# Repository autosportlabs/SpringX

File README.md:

SpringX
======

Strain gauge amplifier for coil spring strain gauges. Spring strain is related to force and compression, and can be used to dynamically determine suspension position.

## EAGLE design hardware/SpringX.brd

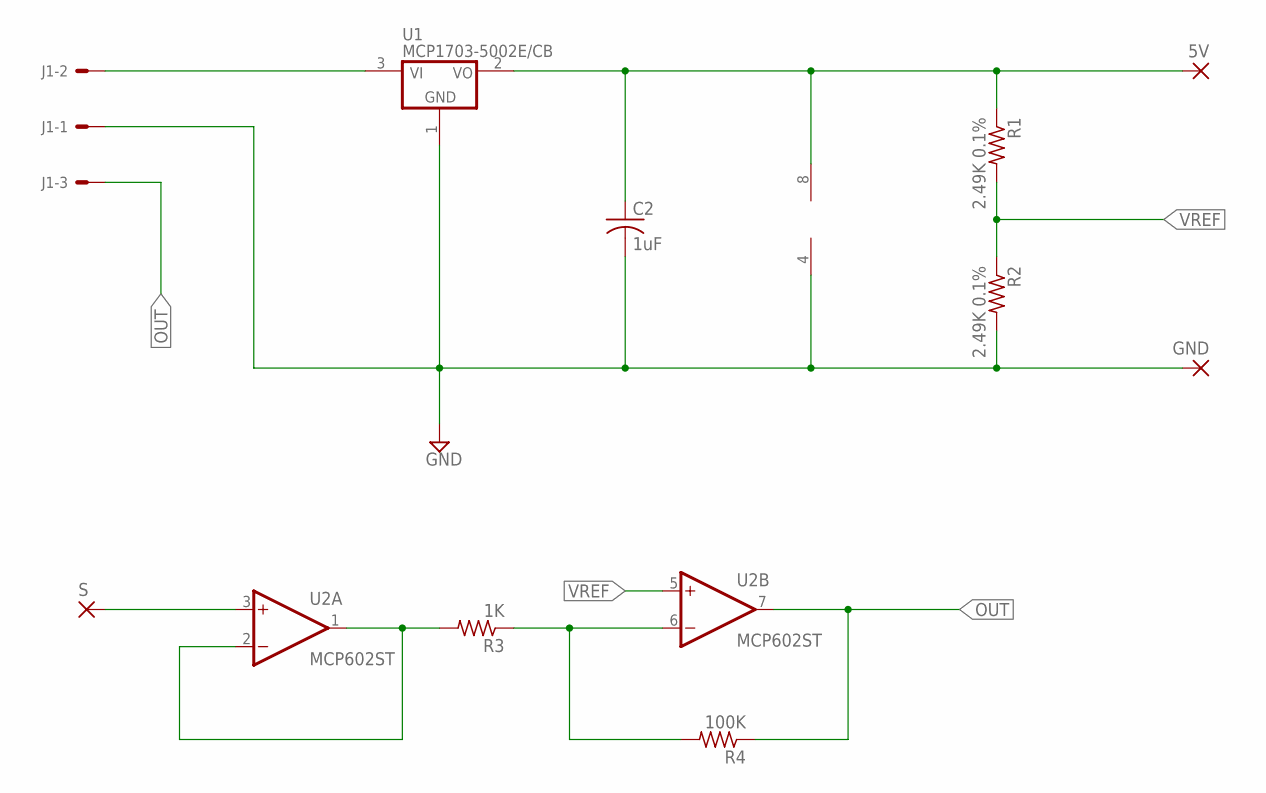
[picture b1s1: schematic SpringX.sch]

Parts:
5V: 2,15/1,0
C2: 1uF; C0603
GND: 2,15/1,0
J1: 22-05-7038-03; 7395-03
R1, R2: 2.49K 0.1%; R0603
R3: 1K; R0603
R4: 100K; R0603
S: 2,15/1,0
U1: MCP1703-5002E/CB; SOT23A_MICROCHIP_CB
U2: MCP602ST; TSSOP8

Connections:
5V: 5V.1, C2.1, R1.1, U1.2 (VO), U2.8 (V+)
GND: C2.2, GND.1, J1.1, R2.2, U1.1 (GND), U2.4 (V-)
unnamed: R3.2, U2.1 (OUT), U2.2 (-IN)
unnamed: S.1, U2.3 (+IN)
unnamed: R3.1, R4.2, U2.6 (-IN)
OUT: J1.3, R4.1, U2.7 (OUT)
VI: J1.2, U1.3 (VI)
VREF: R1.2, R2.1, U2.5 (+IN)

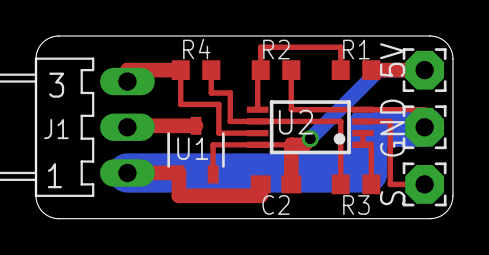
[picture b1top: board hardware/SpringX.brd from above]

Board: 2 copper layers, 23.2 x 10.2 mm, 11 parts (0 on the bottom side), 8 nets.

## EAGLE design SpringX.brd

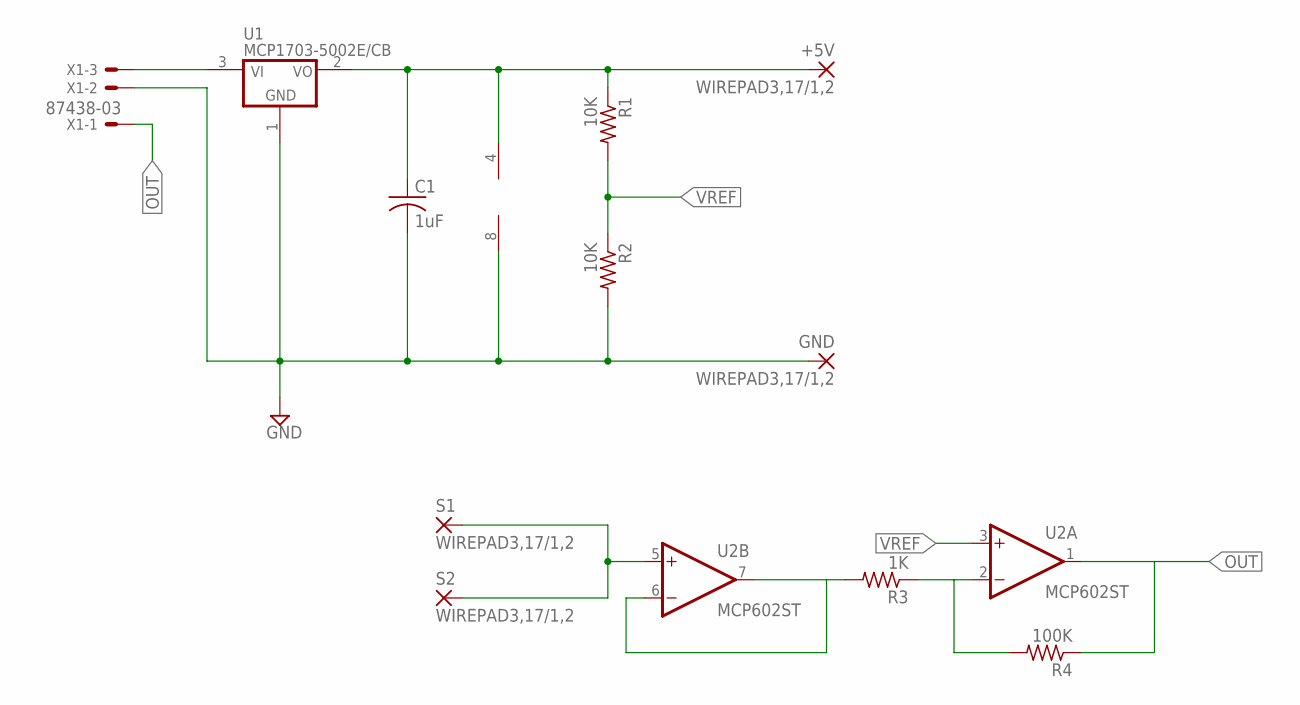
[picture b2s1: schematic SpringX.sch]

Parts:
+5V: WIREPAD3,17/1,2; 3,17/1,2
C1: 1uF; C0603
GND: WIREPAD3,17/1,2; 3,17/1,2
R1, R2: 10K; R0603
R3: 1K; R0603
R4: 100K; R0603
S1, S2: WIREPAD3,17/1,2; 3,17/1,2
U1: MCP1703-5002E/CB; SOT23A_MICROCHIP_CB
U2: MCP602ST; TSSOP8
X1: 87438-03

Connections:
5V: +5V.1, C1.1, R1.1, U1.2 (VO), U2.4 (V-)
GND: C1.2, GND.1, R2.2, U1.1 (GND), U2.8 (V+), X1.2
unnamed: U1.3 (VI), X1.3
unnamed: R3.2, U2.6 (-IN), U2.7 (OUT)
unnamed: R3.1, R4.2, U2.2 (-IN)
OUT: R4.1, U2.1 (OUT), X1.1
STR: S1.1, S2.1, U2.5 (+IN)
VREF: R1.2, R2.1, U2.3 (+IN)

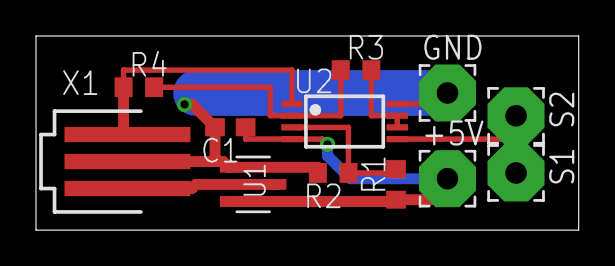
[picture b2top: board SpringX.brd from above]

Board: 2 copper layers, 30.1 x 10.8 mm, 12 parts (0 on the bottom side), 8 nets.

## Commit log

2014-02-19 Initial version of schematic and board under development.
2014-02-19 Revised board layout to use solder pads for strain gauges and Molex PICO-SPOX connector for car interface.
2014-02-22 Re-arranged board layout to reduce width. This will allow the board to be passed through smaller holes in bodywork while permanently connected to the spring.
2014-02-22 Created hardware folder and moved design files to it.
2014-02-22 Removed old design file locations (moved to /hardware).
2014-02-23 minor tweaks to labels placement / size, board dimension and schematics
2014-02-23 Updated file version to Eagle 6.5.0.
2014-03-14 Major revision to board. Corrected error - Op amp power and ground pins reversed Changed to Molex KK connector type. Complete board re-layout.
